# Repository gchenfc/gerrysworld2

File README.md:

This is the source code for my personal website.
It is hosted on pages.github.com at
	gerry-chen.github.io
and accessible via
	gerry-chen.com

and also mirrored at
	gchenfc.github.io
and accessible via
	gerrysworld.tk

The source code can be found at
	https://github.com/gchenfc/gchenfc.github.io

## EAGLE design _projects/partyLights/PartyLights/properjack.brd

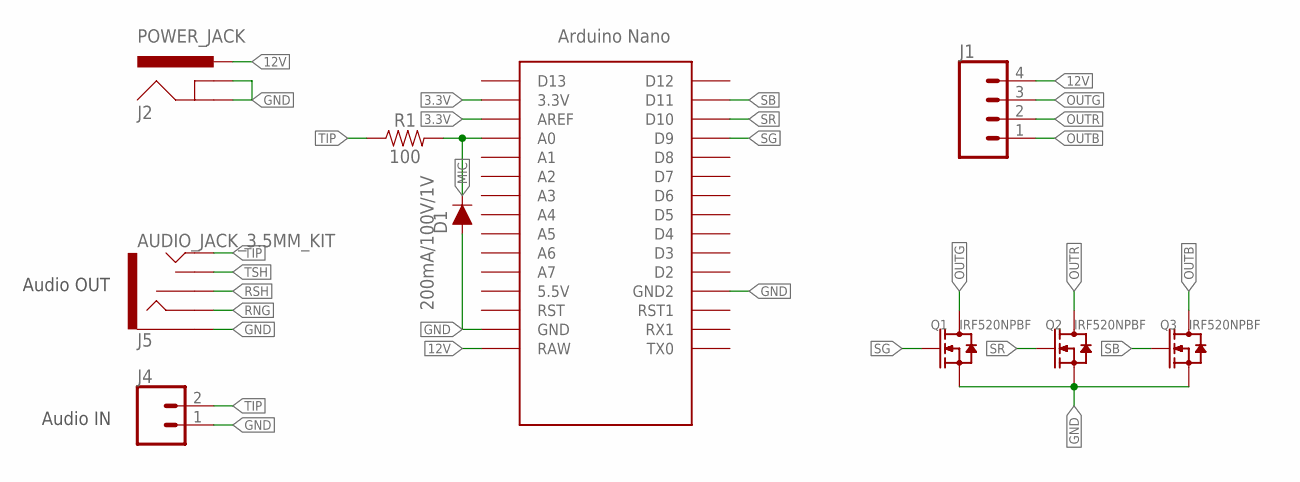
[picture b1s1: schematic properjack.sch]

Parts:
D1: 200mA/100V/1V; DIODE-1N4148
J1: CONN_04LOCK_LONGPADS; 1X04_LOCK_LONGPADS
J2: POWER_JACK; POWER_JACK_PTH
J4: CONN_02LOCK_LONGPADS; 1X02_LOCK_LONGPADS
J5: AUDIO_JACK_3.5MM_KIT; AUDIO-JACK-KIT
Q1, Q2, Q3: IRF520NPBF; TO-220
R1: 100; AXIAL-0.3
U$1: NANONOICSP; NANO_2

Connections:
3.3V: U$1.3.3V, U$1.AREF
12V: J1.4, J2.PWR, U$1.RAW
GND: D1.A, J2.GND, J2.GNDBREAK, J4.1, J5.SLEEVE, Q1.3 (S), Q2.3 (S), Q3.3 (S), U$1.GND, U$1.GND1 (GND2)
MIC: D1.C, R1.P$2 (2), U$1.A0
OUTB: J1.1, Q3.2 (D), Q3.HEAT (D)
OUTG: J1.3, Q1.2 (D), Q1.HEAT (D)
OUTR: J1.2, Q2.2 (D), Q2.HEAT (D)
RNG: J5.RING
RSH: J5.RSH
SB: Q3.1 (G), U$1.D11
SG: Q1.1 (G), U$1.D9
SR: Q2.1 (G), U$1.D10
TIP: J4.2, J5.TIP, R1.P$1 (1)
TSH: J5.TSH

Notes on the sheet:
Audio IN
Audio OUT

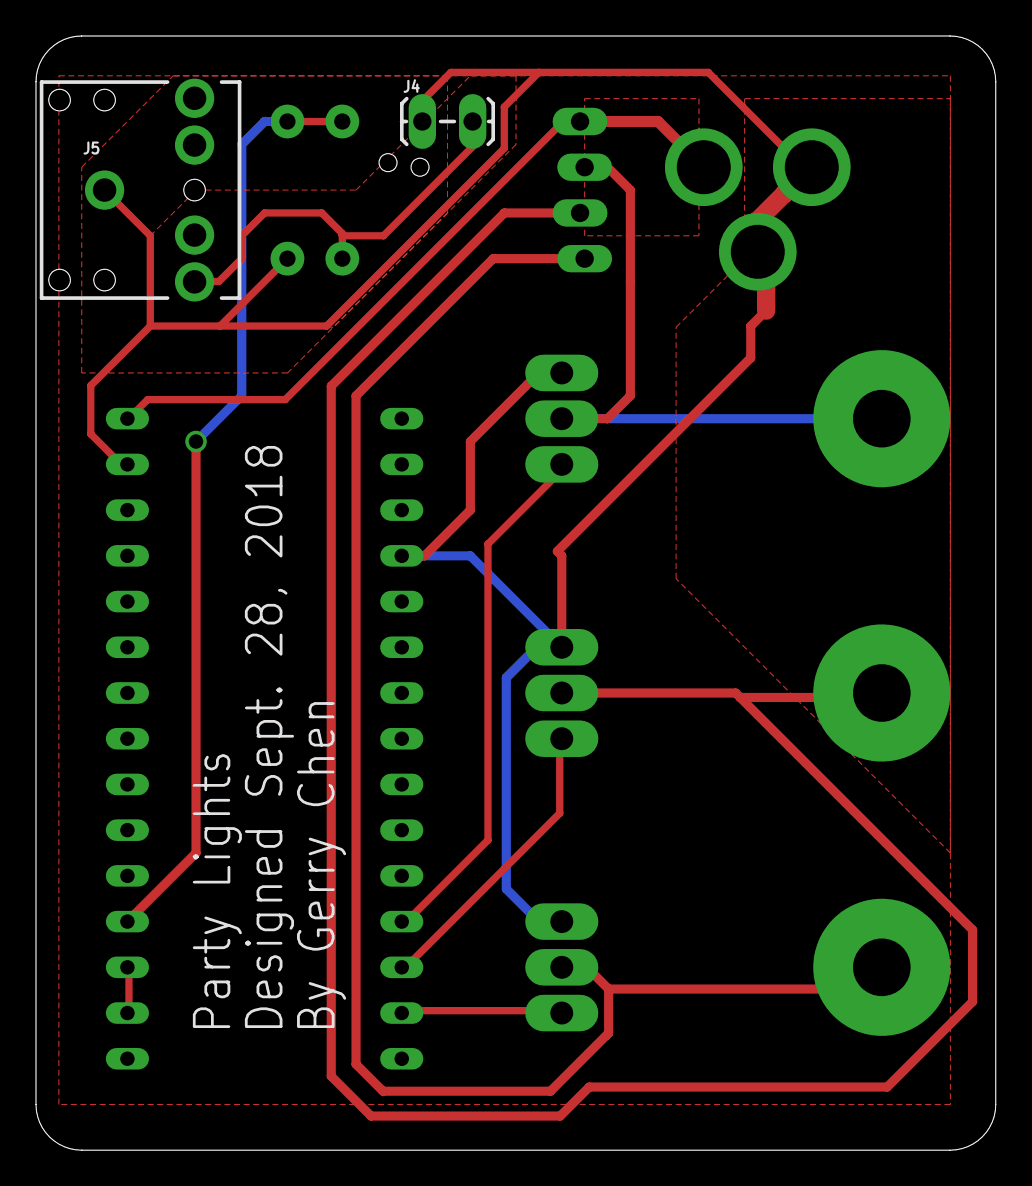
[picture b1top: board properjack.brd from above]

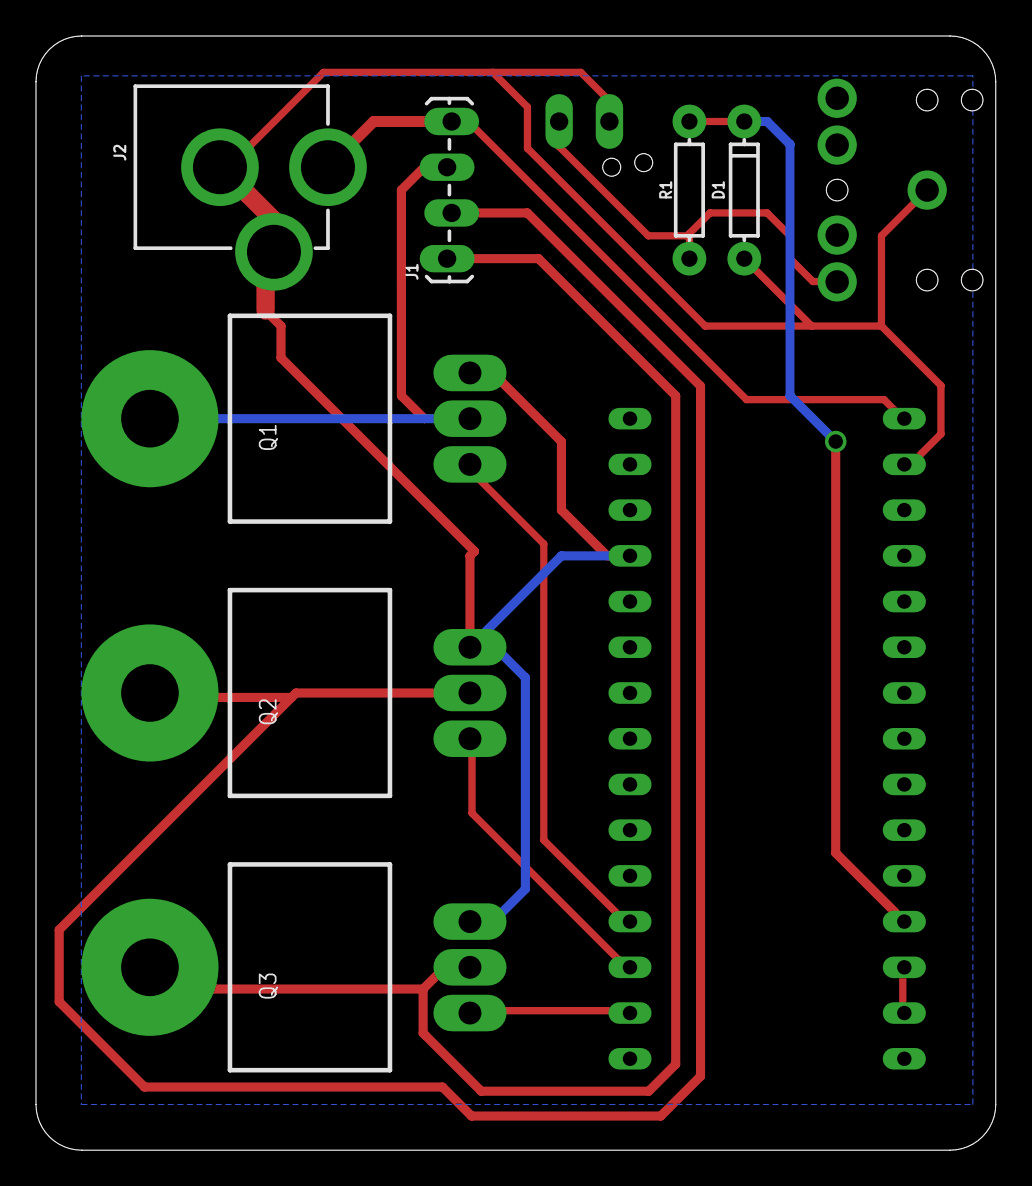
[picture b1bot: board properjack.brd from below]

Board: 2 copper layers, 53.3 x 61.9 mm, 10 parts (8 on the bottom side), 11 nets.

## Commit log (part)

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2021-12-10 diffvg+CLIP
2021-12-10 fix typos
2021-12-10 reformat diffvg+CLIP project description to be shorter
2021-12-10 more specific date
2022-01-03 bulb changer (a few TODO's but almost done)
2022-01-03 duplicate bulbChanger as blog entry
2022-01-03 remove exif data
2022-01-03 build rake
2022-01-03 do what dependabot says
2022-01-03 insert instructables link
2022-01-03 Remove EXIF data (#3)
    * remove exif data
    * build rake
    * add "build" to rakefile
2022-01-10 change broken google photos link to youtube
2022-01-10 include kramdown-parser-gfm (used to be built-in)
2022-01-10 Merge fix/security into master: Follow github's security advice (#4)
    * do what dependabot says
    * include kramdown-parser-gfm (used to be built-in)
2022-01-20 add "Skip navigation" link based on https://youtu.be/jDDaOFr9nqQ
2022-01-20 add "Skip navigation" link based on https://youtu.be/jDDaOFr9nqQ (#5)
2022-01-20 smooth scrolling
2022-01-20 update homepage current education, lol I forgot to update for so long
2022-01-29 update css for code syntax highlighting
2022-01-29 update css to fix mathjax previously, the `*` was adding line spacing and margins to everything which was messing up mathjax
2022-01-29 revert to normal spacing on h2 headers of blogPost
2022-01-29 remove pygments requirements.txt
2022-01-29 blog post about Miller-Rabin primality test
2022-01-29 blog update: added link to rosettacode
2022-01-29 blog post updates
2022-01-29 fix mistake in blog post
2022-02-01 update: ICRA2021 graffiti paper was accepted
2022-02-08 Resume & CV updates
2022-03-02 iros submission
2022-04-12 add GTGraffiti youtube video
2022-04-12 change publication img css / formatting
2022-04-12 add hydroponics poster from CS 8750
2022-04-15 blog entry - calculating travel costs
2022-04-15 fix some typos in blog post 2022-04-15
2022-04-15 add scroll bar on labeled equation
2022-04-21 collapsible box (e.g. for table of contents)
2022-04-21 segfault coredump blog post
2022-04-22 update profile picture
2022-05-06 hydroponics 8750 final report
2022-05-13 200 redirect cs3630 teaching page
2022-05-13 Try to redirect css files
2022-05-13 undo subfolder redirects - doesn't work without trailing slashes https://answers.netlify.com/t/bug-in-non-trailing-slash-rewrite/452/45
2022-05-25 ICRA paper (final)
2022-05-25 ICRA poster GTGraffiti
2022-06-09 add media article links to GTGraffiti
2022-06-09 add published MMSPC paper
2022-06-13 update CV
2022-06-13 remove unnecessary part of url, and add channel 2 news
2022-06-24 blogpost on datascraping
2022-06-24 fix date on datascraping blog post
2022-07-01 iros publications accepted
2022-07-01 random git stuff
2022-07-02 (old) ece 350 final project
2022-07-02 center project titles on projects page
2022-07-02 fix "about me" page formatting
2022-07-05 change footer horiz scrolling behavior
2022-07-05 update "Teaching" in Activities page, and center boxes
2022-07-11 create pages for all publications by default
2022-07-11 add graffiti links
2022-07-28 easy google photos carousel!!!
2022-07-28 readme for googlephoto carousel
2022-07-28 cut-and-fold blog post
2022-07-28 custom shot glasses
2022-07-28 projector screen
2022-07-28 chocolate making
2022-07-29 Geiger dice
2022-07-29 typo
2022-08-01 update final version of iros paper
2022-08-01 auto-embed pdf in publication pages
2022-08-02 iros paper arxiv link
2022-08-04 correct dates
2022-08-22 airplane internet blog post
2022-09-08 fix math study groups end
2022-09-19 create (but not fill-in content) for The Loop page.
2022-09-23 IROS presentation video
2022-09-24 hydroponics paper video
2022-09-27 fix hydroponics icra paper link
2022-11-04 custom ruby filter to handle rel/abs image urls better
2022-11-04 use jekyll plugin for redirect instead of manual http refresh
2022-11-04 add break timer
2022-11-04 update url filter to also allow links relative to site root
2022-11-04 add "Cheer Me Up" alexa skill
2022-11-04 update CV photo ad remove unused files
2022-11-04 food waste pie chart
2022-11-28 urdb selector for Virginia
2022-11-28 add "Utility Name" to URDB rate picker
2022-11-30 update resume
2022-11-30 Change CV/resume download behavior
2022-12-01 Fair Dice Tester project, Pt 1
2022-12-01 add "relevant publications" to hydroponics and graffiti project pages
2022-12-01 Plant Volume measurement with water displacement blog post
2022-12-01 Trying to fix redirects
2022-12-01 Secret Santa 2022
2022-12-05 remove Keith from Secret Santa
2022-12-07 Add Simkl feed using serverless functions and DynamoDB to cache Simkl API results
2022-12-07 blog post on how I made the Serverless Simkl table
2022-12-07 add debug console logs to scheduled simkl feed getter
2022-12-07 make AWS upload synchronous so process doesn't die before upload
2022-12-07 fix Simkl query to also get "watching" and annotate "progress" bar. Previously, Simkl query was only asking for "completed" shows.
2022-12-19 fix typo
2022-12-19 blogpost about Arrow's Impossibility Theorem
2022-12-19 Add earlier reference to Arrow's Impossibility Theorem
2022-12-19 don't justify blog titles in cards
2022-12-27 blog post, quarto, bootstrap
2022-12-27 make common.css less overpowered
2022-12-27 comment-out alternate way I could have done the quarto styling
2022-12-28 Add IROS 2022 DOI links
2023-01-12 Remove "in press" since IROS papers have been published
2023-01-17 Update that ICRA papers were accepted
2023-02-08 Add ASME article about graffiti bot
2023-03-01 add business card to about page
2023-03-01 make business card landing page (redirect to about for now)
2023-04-10 Bump xml2js and aws-sdk
    Bumps [xml2js](https://github.com/Leonidas-from-XIV/node-xml2js) to 0.5.0 and updates ancestor dependency [aws-sdk](https://github.com/aws/aws-sdk-js). These dependencies need to be updated together.
    Updates `xml2js` from 0.4.19 to 0.5.0
    - [Release notes](https://github.com/Leonidas-from-XIV/node-xml2js/releases)
    - [Commits](https://github.com/Leonidas-from-XIV/node-xml2js/compare/0.4.19...0.5.0)
    Updates `aws-sdk` from 2.1269.0 to 2.1354.0
    - [Release notes](https://github.com/aws/aws-sdk-js/releases)
2023-05-02 playing with NeRF blog post
2023-05-02 change google drive links to "view" instead of download
2023-05-02 Remove images by request of subject (updated via google drive)
2023-05-04 Change hydroponics gifs to transparent
2023-06-01 hydroponics poster
2023-06-01 add a video to hydroponics
2023-06-07 add chatgpt link
2023-09-20 update doi's from ICRA 2023
2023-09-20 icra 2024 submission: qopp
2023-09-22 Upload QOPP video to youtube
2023-09-22 Add paper abstracts to paper webpages
2023-09-24 Blog: Busiest Air Travel Days
2023-09-24 Add plot title
2023-09-24 fix bug where single-month-at-a-time broke, and sort years left-right increasing
2023-09-24 blog post Default to include covid with scale
2023-10-03 partial blog post on Kelly Criterion
2023-10-03 make footnotes shorter so they don't go off the side of the page
2023-10-12 biofuel blog post
2023-10-12 Rename some blog posts with a description in the filename/url
2023-10-15 Turn descriptions into plaintext in blogPost "Description" meta
2023-10-15 Make collapsible "input" hiding more selective
2023-10-15 Blog post on "Add-1" brain test
2023-10-15 Make a note about "hearing" vs "seeing" the numbers.
2023-10-15 formatting update to blogpost
2023-10-22 blog post on Airline Revenues
2023-10-30 Post tinyTakeout chip on projects/blog
2023-10-30 tinyTapeout start-to-finish time (3 hrs)
2023-10-31 zoox patent
2023-11-08 Update resume & CV
2023-11-08 Add hyperspectral NeRF stuff
2023-11-08 Add PhD proposal
2023-11-13 Create jekyll plugin tag for "collapsible" block
2023-11-13 progress checkpoint on Square-1 project
2023-11-13 Finish Square-1 project post
2023-11-13 Finish Square-1 post
2023-11-13 fix typos in square-1
2023-11-13 Modify collapsible plugin to make title optional (use first heading in content if not specified)
2023-11-14 Add live photo of completed cube to Square-1 post
2023-11-17 Update CV and resume
2023-12-29 Add Aven book to blog
2023-12-29 exclude "exclude: true" from blog collection
2023-12-29 Add google photos full-res album
2024-01-30 mark QOPP paper as accepted
2024-03-03 final qopp pdf
2024-03-21 Update menu bar to be clickable across width of buttons
2024-03-21 move stuff from git lfs to google drive to reduce load on github lfs limits
2024-03-21 Add HS-NeRF paper
2024-03-21 add RAW-AIR iros paper, and fix pdf absolute link
2024-03-21 fix jekyll warning
2024-03-21 draft of blog post about house buying analytics that I abandoned bc I found zillow had one but actually i don't trust Zillow
2024-03-25 update HS-NeRF with arxiv link
2024-03-28 meta tags for "og" (social media tags)
2024-04-08 house buying draft progress - javascript getting closer
2024-04-08 refactored functions into different files and split creation into create/update
2024-04-08 Cleaning up and preliminarily done with blog post
2024-04-16 house buying claude3 for posterity
2024-04-16 QR code generation quick reference
2024-04-17 Elimination animation
2024-04-17 Upload QOPP poster
2024-04-29 update poster font
2024-06-12 Blog post on AMF practice quiz
2024-06-12 upload RSS workshop paper
2024-07-11 Update Chen24rss and Chen24iros acceptances & poster
2024-07-11 Update MMSPC paper thumbnail
2024-07-11 Locally download DCEA paper, but gitignore it for copyright
2024-07-15 Add diffusion painting live demo link and other links
2024-07-25 draft, working but want to specify column/row orientation to sort (up/down)
2024-07-25 latex table colorizer improved
2024-07-25 little improvements, and complete :)
2024-07-25 Bump xml2js and aws-sdk
    Bumps [xml2js](https://github.com/Leonidas-from-XIV/node-xml2js) to 0.6.2 and updates ancestor dependency [aws-sdk](https://github.com/aws/aws-sdk-js). These dependencies need to be updated together.
    Updates `xml2js` from 0.4.19 to 0.6.2
    - [Commits](https://github.com/Leonidas-from-XIV/node-xml2js/compare/0.4.19...0.6.2)
    Updates `aws-sdk` from 2.1269.0 to 2.1664.0
    - [Release notes](https://github.com/aws/aws-sdk-js/releases)
    - [Commits](https://github.com/aws/aws-sdk-js/compare/v2.1269.0...v2.1664.0)
2024-07-25 fix latex colorizer mathjax load order
2024-08-09 Add DOI for ICRA 2024 QOPP paper
2024-08-11 initial page for thesis
2024-08-11 Upload ics file for thesis defense
2024-08-14 Change "ECCV" paper in review to "3DV"
2024-08-19 Add TEDx Talk and update Thesis links
2024-11-03 blog post on reviving a dead usb battery bank
2025-06-24 Ear socks blog post
2025-08-19 update projects, about, publications, etc.
2025-09-14 Create simple carousel (with ChatGPT)
2025-09-14 Add blogpost for car headliner
2025-09-14 Add amazon affiliate link
2025-09-15 add tags
2025-09-15 Add jekyll sitemap
2026-03-28 Blog post for quick 3d printed hairdryer holder
2026-03-28 Add skills directory
2026-03-28 pin ruby version to try to fix netlify deploy
2026-03-29 switch snowman png to smaller jpg which is visually indistinguishable
2026-03-29 Test updating ruby and jekyll versions
2026-03-29 Fix date on a blogpost
2026-03-29 remove .gemini symlink
2026-03-29 Tweaks to restore parity with pre-version bump
2026-03-29 Remove unnecessary exclude changes
2026-04-08 Bump addressable from 2.8.9 to 2.9.0
    Bumps [addressable](https://github.com/sporkmonger/addressable) from 2.8.9 to 2.9.0.
    - [Changelog](https://github.com/sporkmonger/addressable/blob/main/CHANGELOG.md)
    - [Commits](https://github.com/sporkmonger/addressable/compare/addressable-2.8.9...addressable-2.9.0)
    ---
    updated-dependencies:
    - dependency-name: addressable

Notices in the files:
parts and their libraries:
SparkFun-DiscreteSemi: Licensing: Creative Commons ShareAlike 4.0 International - https://creativecommons.org/licenses/by-sa/4.0
